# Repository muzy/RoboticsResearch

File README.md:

RoboticsResearch
================

Build a sustainable open-source robot platform affordable for everyone. This project is part of a student research project at the DHBW Mannheim, Germany.

ToDo
----

- [x] Create Repository 
- [X] Finish Introduction
- [WIP] Evaluation of the "state of the art"
- [WIP] Case studies
- [ ] Prototype 
- [ ] Prototype testing with designated target group
- [ ] Documentation

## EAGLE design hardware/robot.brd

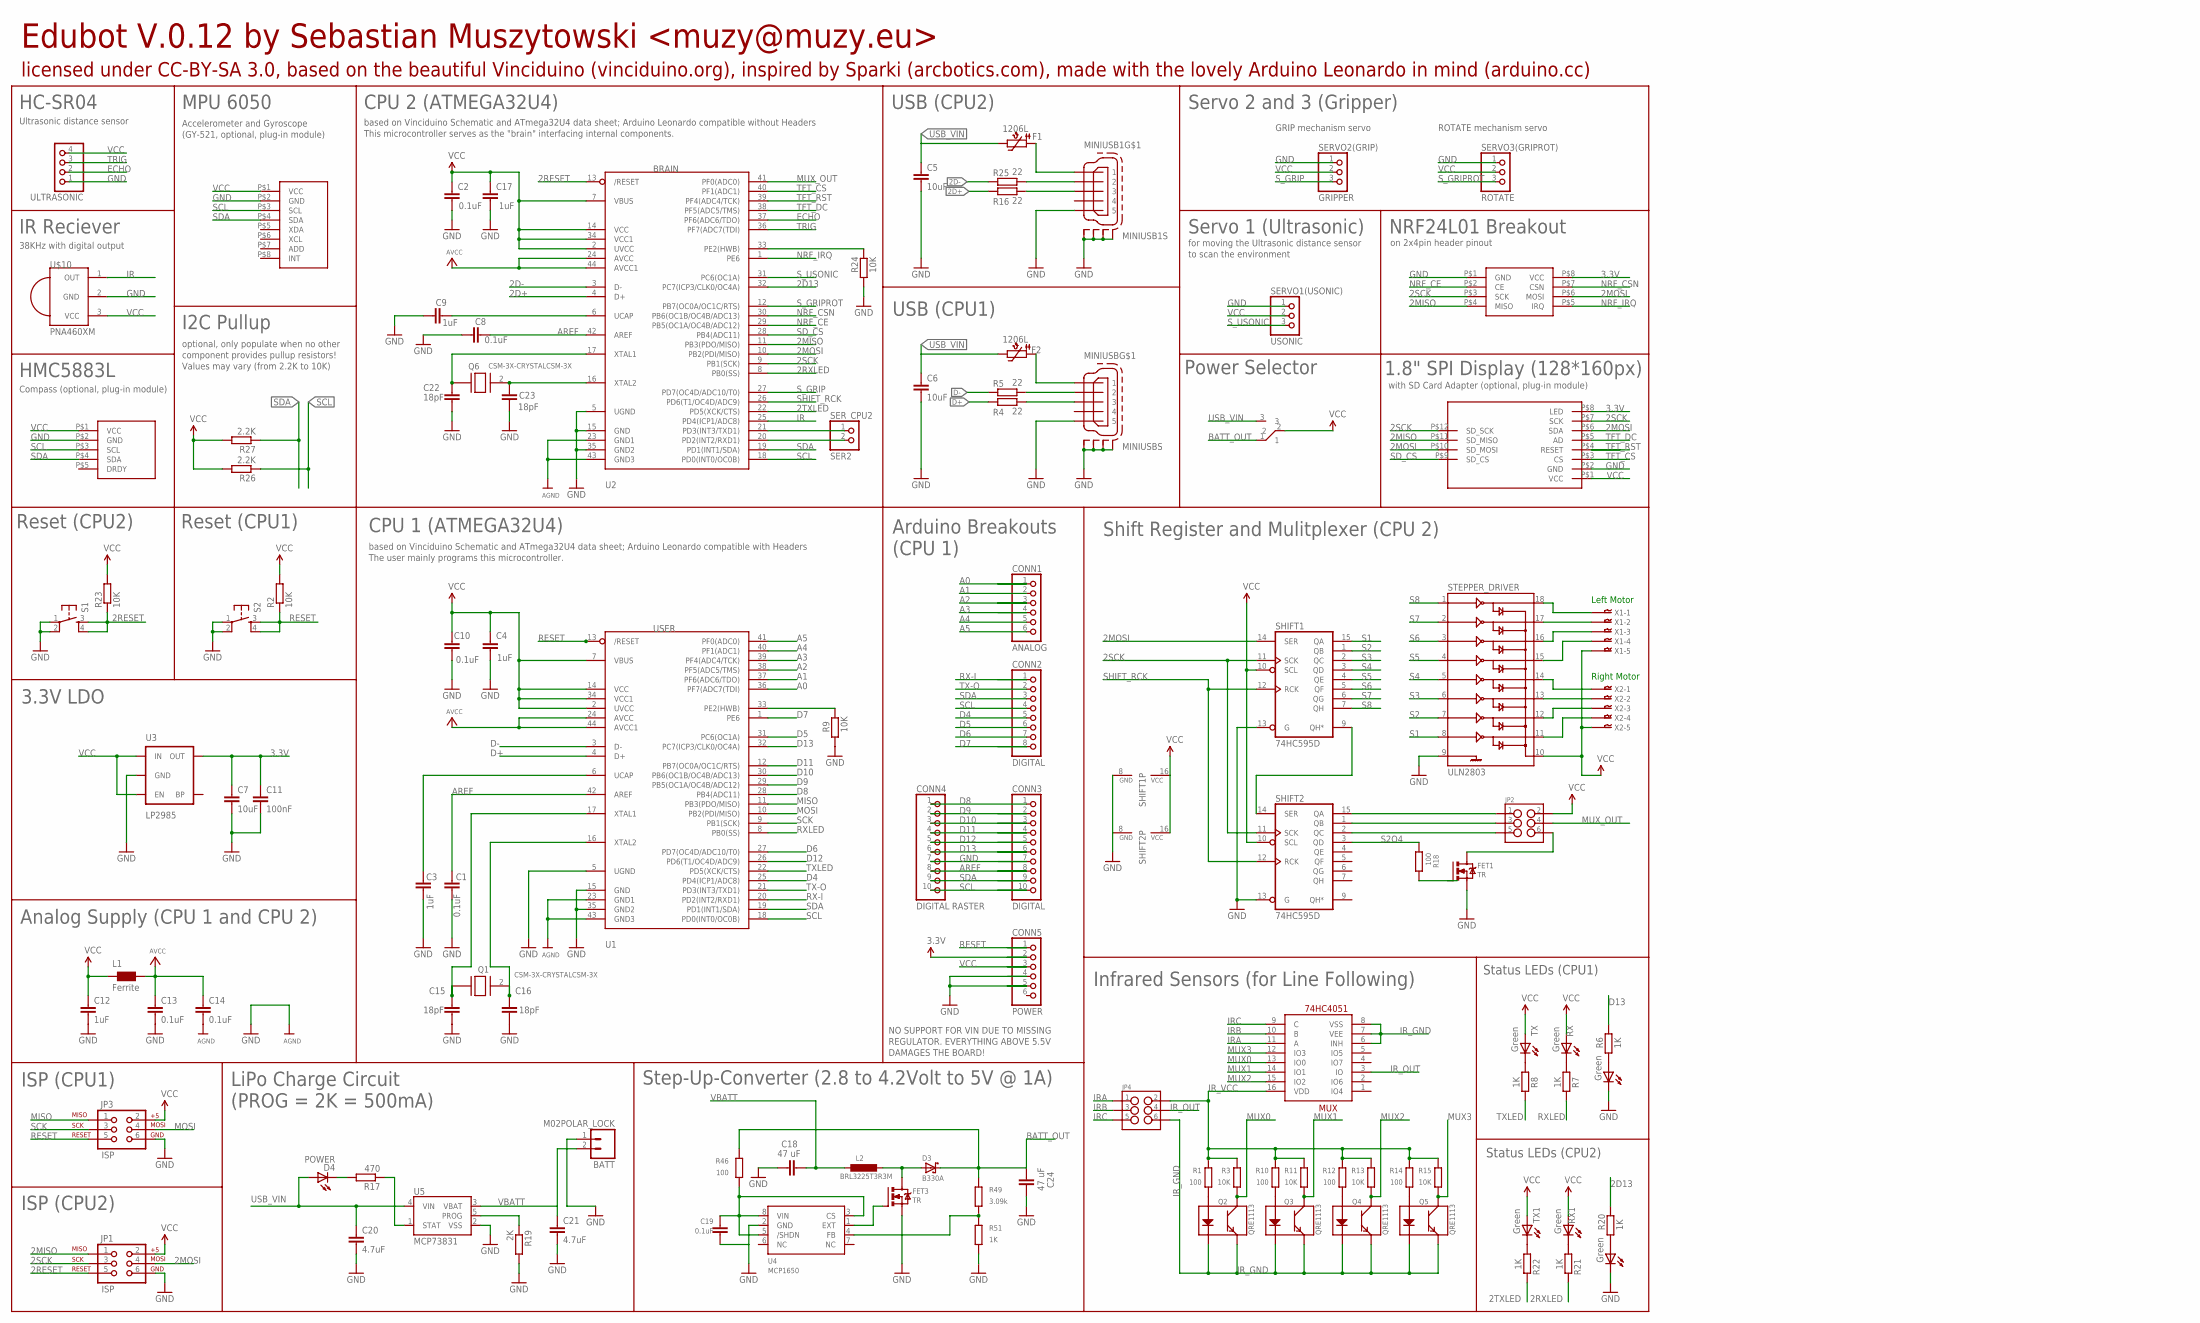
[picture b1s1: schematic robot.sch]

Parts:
BATT: M02POLAR_LOCK; MOLEX-1X2_LOCK
C1, C2, C8, C10, C13, C14, C19: 0.1uF; C1206
C3, C4, C9, C12, C17: 1uF; C1206
C5, C6, C7: 10uF; C1206
C11: 100nF; C1206
C15, C16, C22, C23: 18pF; C1206
C18, C24: 47 uF; C1206
C20, C21: 4.7uF; C1206
CONN1: ANALOG; 1X06-BIG
CONN2: DIGITAL; 1X08-BIG
CONN3: DIGITAL; 1X10-BIG
CONN4: DIGITAL RASTER; 1X10-BIG
CONN5: POWER; 1X06-BIG
D3: B330A; SMA
D4: POWER; LED-1206
D13, D13_2: Green; LED-1206
F1, F2: 1206L; 1206_PTC
FET1, FET3: TR; MICRO3
JP1, JP3: ISP; 2X3
JP2, JP4: M03X22X3_SILK_SM; 2X3
L1: Ferrite; 1206W
L2: BRL3225T3R3M; L3225P
MINIUSB, MINIUSB1: MINI-USB-SCHIELD-32005-201; 32005-201
MUX: 74HC4051; SO16
Q1, Q6: CSM-3X-CRYSTALCSM-3X; CSM-3X
Q2, Q3, Q4, Q5: QRE1113
R1, R10, R12, R14, R18, R46: 100; R1206
R2, R3, R9, R11, R13, R15, R23, R24: 10K; R1206
R4, R5, R16, R25: 22; R1206
R6, R7, R8, R20, R21, R22, R51: 1K; R1206
R17: 470; R1206
R19: 2K; R1206
R26, R27: 2.2K; R1206
R49: 3.09k; R1206
RX, RX1: Green; LED-1206
S1, S2: Reset; TACTILE_SWITCH_SMD
SERVO1(USONIC): USONIC; 1X03
SERVO2(GRIP): GRIPPER; 1X03
SERVO3(GRIPROT): ROTATE; 1X03
SER_CPU2: SER2; 1X02
SHIFT1, SHIFT2: 74HC595D; SO16
STEPPER_DRIVER: ULN2803; SO18L
SW1: SPDT; SPDT-PTH
TX, TX1: Green; LED-1206
U1: USER; TQFP44
U2: BRAIN; TQFP44
U3: LP2985; SOT23-5@1
U4: MCP1650; MSOP8
U5: MCP73831; SOT23-5
U$2: 1.8TFT+SD; 1.8TFTSD
U$3: GY-521
U$4: HMC5883L
U$5: NRF24L01+
U$10: PNA460XM
ULTRASONIC: PINHD-1X4; 1X04
X1, X2: 05-JST-B5B-XH-A; B5B-XH

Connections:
2D13: R20.1, U2.32 (PC7(ICP3/CLK0/OC4A))
2D+: R16.1, U2.4 (D+)
2D-: R25.1, U2.3 (D-)
2MISO: JP1.1, U2.11 (PB3(PDO/MISO)), U$2.P$11 (SD_MISO), U$5.P$4 (MISO)
2MOSI: JP1.4, SHIFT1.14 (SER), U2.10 (PB2(PDI/MISO)), U$2.P$6 (SDA), U$2.P$10 (SD_MOSI), U$5.P$6 (MOSI)
2RESET: JP1.5, R23.1, S1.3, S1.4, U2.13 (/RESET)
2RXLED: R21.1, U2.8 (PB0(SS))
2SCK: JP1.3, SHIFT1.11 (SCK), SHIFT2.11 (SCK), U2.9 (PB1(SCK)), U$2.P$7 (SCK), U$2.P$12 (SD_SCK), U$5.P$3 (SCK)
2TXLED: R22.1, U2.22 (PD5(XCK/CTS))
2XTAL1: C22.1, Q6.1, U2.17 (XTAL1)
2XTAL2: C23.1, Q6.2, U2.16 (XTAL2)
3.3V: C7.1, C11.1, CONN5.2, U3.5 (OUT), U$2.P$8 (LED), U$5.P$8 (VCC)
A0: CONN1.1, U1.36 (PF7(ADC7(TDI))
A1: CONN1.2, U1.37 (PF6(ADC6/TDO))
A2: CONN1.3, U1.38 (PF5(ADC5/TMS))
A3: CONN1.4, U1.39 (PF4(ADC4/TCK))
A4: CONN1.5, U1.40 (PF1(ADC1))
A5: CONN1.6, U1.41 (PF0(ADC0))
AREF: C1.2, C8.2, CONN3.8, CONN4.8, U1.42 (AREF), U2.42 (AREF)
AVCC: C13.1, C14.1, L1.2, U1.24 (AVCC), U1.44 (AVCC1), U2.24 (AVCC), U2.44 (AVCC1)
BATT_OUT: C24.1, D3.C, R46.2, R49.2, SW1.1
D4: CONN2.5, U1.25 (PD4(ICP1/ADC8))
D5: CONN2.6, U1.31 (PC6(OC1A))
D6: CONN2.7, U1.27 (PD7(OC4D/ADC10/T0))
D7: CONN2.8, U1.1 (PE6)
D8: CONN3.1, CONN4.1, U1.28 (PB4(ADC11))
D9: CONN3.2, CONN4.2, U1.29 (PB5(OC1A/OC4B/ADC12))
D10: CONN3.3, CONN4.3, U1.30 (PB6(OC1B/OC4B/ADC13))
D11: CONN3.4, CONN4.4, U1.12 (PB7(OC0A/OC1C/RTS))
D12: CONN3.5, CONN4.5, U1.26 (PD6(T1/OC4D/ADC9))
D13: CONN3.6, CONN4.6, R6.1, U1.32 (PC7(ICP3/CLK0/OC4A))
D+: R4.1, U1.4 (D+)
D-: R5.1, U1.3 (D-)
ECHO: U2.37 (PF6(ADC6/TDO)), ULTRASONIC.2
GND: BATT.1, C1.1, C2.2, C3.2, C4.2, C5.2, C6.2, C7.2, C8.1, C9.2, C10.2, C11.2, C12.2, C13.2, C14.2, C15.2, C16.2, C17.2, C18.1, C19.2, C20.2, C21.2, C22.2, C23.2, C24.2, CONN3.7, CONN4.7, CONN5.4, CONN5.5, D13.C, D13_2.C, FET1.2 (S), FET3.2 (S), JP1.6, JP3.6, MINIUSB.5, MINIUSB.M1 (S1), MINIUSB.M2 (S2), MINIUSB.M3 (S3), MINIUSB.M4 (S4), MINIUSB1.5, MINIUSB1.M1 (S1), MINIUSB1.M2 (S2), MINIUSB1.M3 (S3), MINIUSB1.M4 (S4), R9.2, R19.2, R24.2, R51.1, S1.1, S1.2, S2.1, S2.2, SERVO1(USONIC).1, SERVO2(GRIP).1, SERVO3(GRIPROT).1, SHIFT1.8 (GND), SHIFT1.13 (G), SHIFT2.8 (GND), SHIFT2.13 (G), STEPPER_DRIVER.9, U1.5 (UGND), U1.15 (GND), U1.23 (GND1), U1.35 (GND2), U1.43 (GND3), U2.5 (UGND), U2.15 (GND), U2.23 (GND1), U2.35 (GND2), U2.43 (GND3), U3.2 (GND), U4.2 (GND), U5.2 (VSS), U$2.P$2 (GND), U$3.P$2 (GND), U$4.P$2 (GND), U$5.P$1 (GND), U$10.2 (GND), ULTRASONIC.1
IR: U2.25 (PD4(ICP1/ADC8)), U$10.1 (OUT)
IRA: JP4.1, MUX.11 (A)
IRB: JP4.3, MUX.10 (B)
IRC: JP4.5, MUX.9 (C)
IR_GND: JP4.6, MUX.6 (INH), MUX.7 (VEE), MUX.8 (VSS), Q2.2 (K), Q2.4 (E), Q3.2 (K), Q3.4 (E), Q4.2 (K), Q4.4 (E), Q5.2 (K), Q5.4 (E)
IR_OUT: JP4.4, MUX.3 (IO)
IR_VCC: JP4.2, MUX.16 (VDD), R1.2, R3.2, R10.2, R11.2, R12.2, R13.2, R14.2, R15.2
MISO: JP3.1, U1.11 (PB3(PDO/MISO))
MOSI: JP3.4, U1.10 (PB2(PDI/MISO))
MUX0: MUX.13 (IO0), Q2.3 (C), R3.1
MUX1: MUX.14 (IO1), Q3.3 (C), R11.1
MUX2: MUX.15 (IO2), Q4.3 (C), R13.1
MUX3: MUX.12 (IO3), Q5.3 (C), R15.1
MUX_OUT: JP2.4, U2.41 (PF0(ADC0))
unnamed: R8.2, TX.C
unnamed: MINIUSB.2, R5.2
unnamed: SER_CPU2.1, U2.21 (PD3(INT3/TXD1))
unnamed: SER_CPU2.2, U2.20 (PD2(INT2/RXD1))
unnamed: MINIUSB.3, R4.2
unnamed: R9.1, U1.33 (PE2(HWB))
unnamed: D13.A, R6.2
unnamed: C9.1, U2.6 (UCAP)
unnamed: R7.2, RX.C
unnamed: Q2.1 (A), R1.1
unnamed: Q3.1 (A), R10.1
unnamed: Q4.1 (A), R12.1
unnamed: F2.1, MINIUSB.1
unnamed: Q5.1 (A), R14.1
unnamed: C3.1, U1.6 (UCAP)
unnamed: FET1.1 (G), R18.2
unnamed: R24.1, U2.33 (PE2(HWB))
unnamed: F1.1, MINIUSB1.1
unnamed: FET3.1 (G), U4.1 (EXT)
unnamed: R19.1, U5.5 (PROG)
unnamed: R17.1, U5.1 (STAT)
unnamed: D4.C, R17.2
unnamed: R49.1, R51.2, U4.4 (FB)
unnamed: D3.A, FET3.3 (D), L2.2
unnamed: C19.1, R46.1, U4.3 (CS), U4.5 (/SHDN), U4.8 (VIN)
unnamed: STEPPER_DRIVER.11, X2.P$4
unnamed: STEPPER_DRIVER.12, X2.P$3
unnamed: STEPPER_DRIVER.13, X2.P$2
unnamed: STEPPER_DRIVER.14, X2.P$1
unnamed: STEPPER_DRIVER.15, X1.P$4
unnamed: STEPPER_DRIVER.16, X1.P$3
unnamed: STEPPER_DRIVER.17, X1.P$2
unnamed: STEPPER_DRIVER.18, X1.P$1
unnamed: D13_2.A, R20.2
unnamed: R22.2, TX1.C
unnamed: R21.2, RX1.C
unnamed: MINIUSB1.2, R25.2
unnamed: MINIUSB1.3, R16.2
unnamed: JP2.1, SHIFT2.15 (QA)
unnamed: JP2.3, SHIFT2.1 (QB)
unnamed: JP2.5, SHIFT2.2 (QC)
unnamed: FET1.3 (D), JP2.6
NRF_CE: U2.29 (PB5(OC1A/OC4B/ADC12)), U$5.P$2 (CE)
NRF_CSN: U2.30 (PB6(OC1B/OC4B/ADC13)), U$5.P$7 (CSN)
NRF_IRQ: U2.1 (PE6), U$5.P$5 (IRQ)
RESET: CONN5.1, JP3.5, R2.1, S2.3, S2.4, U1.13 (/RESET)
RX-I: CONN2.1, U1.20 (PD2(INT2/RXD1))
RXLED: R7.1, U1.8 (PB0(SS))
S1: SHIFT1.15 (QA), STEPPER_DRIVER.8
S1OVERFLOW: SHIFT1.9 (QH*), SHIFT2.14 (SER)
S2: SHIFT1.1 (QB), STEPPER_DRIVER.7
S2O4: R18.1, SHIFT2.3 (QD)
S3: SHIFT1.2 (QC), STEPPER_DRIVER.6
S4: SHIFT1.3 (QD), STEPPER_DRIVER.5
S5: SHIFT1.4 (QE), STEPPER_DRIVER.4
S6: SHIFT1.5 (QF), STEPPER_DRIVER.3
S7: SHIFT1.6 (QG), STEPPER_DRIVER.2
S8: SHIFT1.7 (QH), STEPPER_DRIVER.1
SCK: JP3.3, U1.9 (PB1(SCK))
SCL: CONN2.4, CONN3.10, CONN4.10, R26.1, U1.18 (PD0(INT0/OC0B)), U2.18 (PD0(INT0/OC0B)), U$3.P$3 (SCL), U$4.P$3 (SCL)
SDA: CONN2.3, CONN3.9, CONN4.9, R27.1, U1.19 (PD1(INT1/SDA)), U2.19 (PD1(INT1/SDA)), U$3.P$4 (SDA), U$4.P$4 (SDA)
SD_CS: U2.28 (PB4(ADC11)), U$2.P$9 (SD_CS)
SHIFT_RCK: SHIFT1.12 (RCK), SHIFT2.12 (RCK), U2.26 (PD6(T1/OC4D/ADC9))
S_GRIP: SERVO2(GRIP).3, U2.27 (PD7(OC4D/ADC10/T0))
S_GRIPROT: SERVO3(GRIPROT).3, U2.12 (PB7(OC0A/OC1C/RTS))
S_USONIC: SERVO1(USONIC).3, U2.31 (PC6(OC1A))
TFT_CS: U2.40 (PF1(ADC1)), U$2.P$3 (CS)
TFT_DC: U2.38 (PF5(ADC5/TMS)), U$2.P$5 (AD)
TFT_RST: U2.39 (PF4(ADC4/TCK)), U$2.P$4 (RESET)
TRIG: U2.36 (PF7(ADC7(TDI)), ULTRASONIC.3
TX-O: CONN2.2, U1.21 (PD3(INT3/TXD1))
TXLED: R8.1, U1.22 (PD5(XCK/CTS))
USB_VIN: C5.1, C6.1, C20.1, D4.A, F1.2, F2.2, SW1.3, U5.4 (VIN)
VBATT: BATT.2, C18.2, C21.1, L2.1, U5.3 (VBAT)
VCC: C2.1, C4.1, C10.1, C12.1, C17.1, CONN5.3, JP1.2, JP2.2, JP3.2, L1.1, R2.2, R23.2, R26.2, R27.2, RX.A, RX1.A, SERVO1(USONIC).2, SERVO2(GRIP).2, SERVO3(GRIPROT).2, SHIFT1.10 (SCL), SHIFT1.16 (VCC), SHIFT2.10 (SCL), SHIFT2.16 (VCC), STEPPER_DRIVER.10, SW1.2, TX.A, TX1.A, U1.2 (UVCC), U1.7 (VBUS), U1.14 (VCC), U1.34 (VCC1), U2.2 (UVCC), U2.7 (VBUS), U2.14 (VCC), U2.34 (VCC1), U3.1 (IN), U3.3 (EN), U$2.P$1 (VCC), U$3.P$1 (VCC), U$4.P$1 (VCC), U$10.3 (VCC), ULTRASONIC.4, X1.P$5, X2.P$5
XTAL1: C15.1, Q1.1, U1.17 (XTAL1)
XTAL2: C16.1, Q1.2, U1.16 (XTAL2)

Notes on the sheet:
USB (CPU1)
Reset (CPU1)
ISP (CPU1)
Analog Supply (CPU 1 and CPU 2)
Arduino Breakouts (CPU 1)
CPU 1 (ATMEGA32U4)
Left Motor
Right Motor
Shift Register and Mulitplexer (CPU 2)
Infrared Sensors (for Line Following)
Step-Up-Converter (2.8 to 4.2Volt to 5V @ 1A)
LiPo Charge Circuit (PROG = 2K = 500mA)
Status LEDs (CPU1)
Status LEDs (CPU2)
ISP (CPU2)
3.3V LDO
based on Vinciduino Schematic and ATmega32U4 data sheet; Arduino Leonardo compatible with Headers The user mainly programs this microcontroller.
Reset (CPU2)
CPU 2 (ATMEGA32U4)
based on Vinciduino Schematic and ATmega32U4 data sheet; Arduino Leonardo compatible without Headers This microcontroller serves as the "brain" interfacing internal components.
USB (CPU2)
Power Selector
1.8" SPI Display (128*160px)
with SD Card Adapter (optional, plug-in module)
I2C Pullup
optional, only populate when no other component provides pullup resistors! Values may vary (from 2.2K to 10K)
HMC5883L
Compass (optional, plug-in module)
MPU 6050
Accelerometer and Gyroscope (GY-521, optional, plug-in module)
NRF24L01 Breakout
on 2x4pin header pinout
IR Reciever
38KHz with digital output
HC-SR04
Ultrasonic distance sensor
Servo 1 (Ultrasonic)
for moving the Ultrasonic distance sensor to scan the environment
Servo 2 and 3 (Gripper)
GRIP mechanism servo

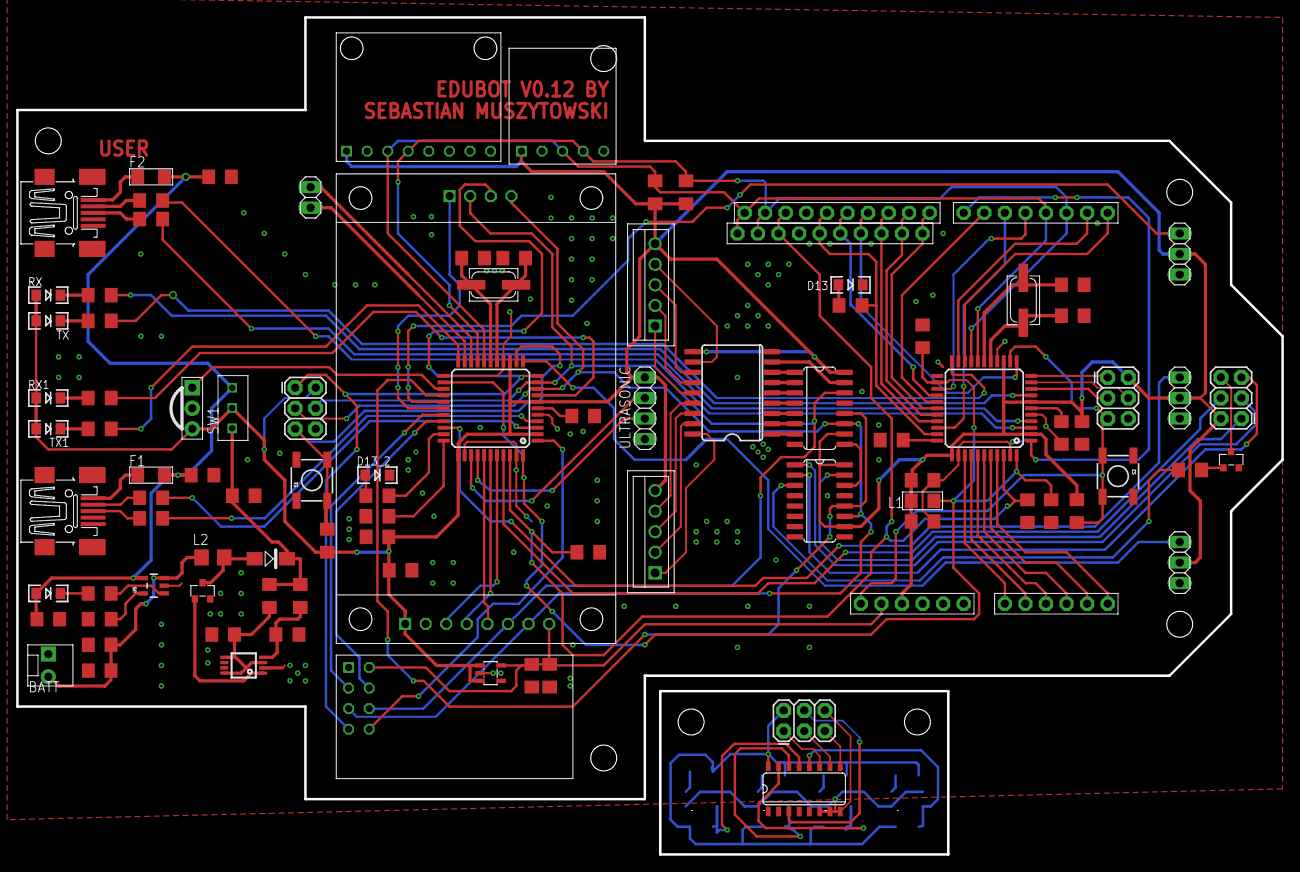
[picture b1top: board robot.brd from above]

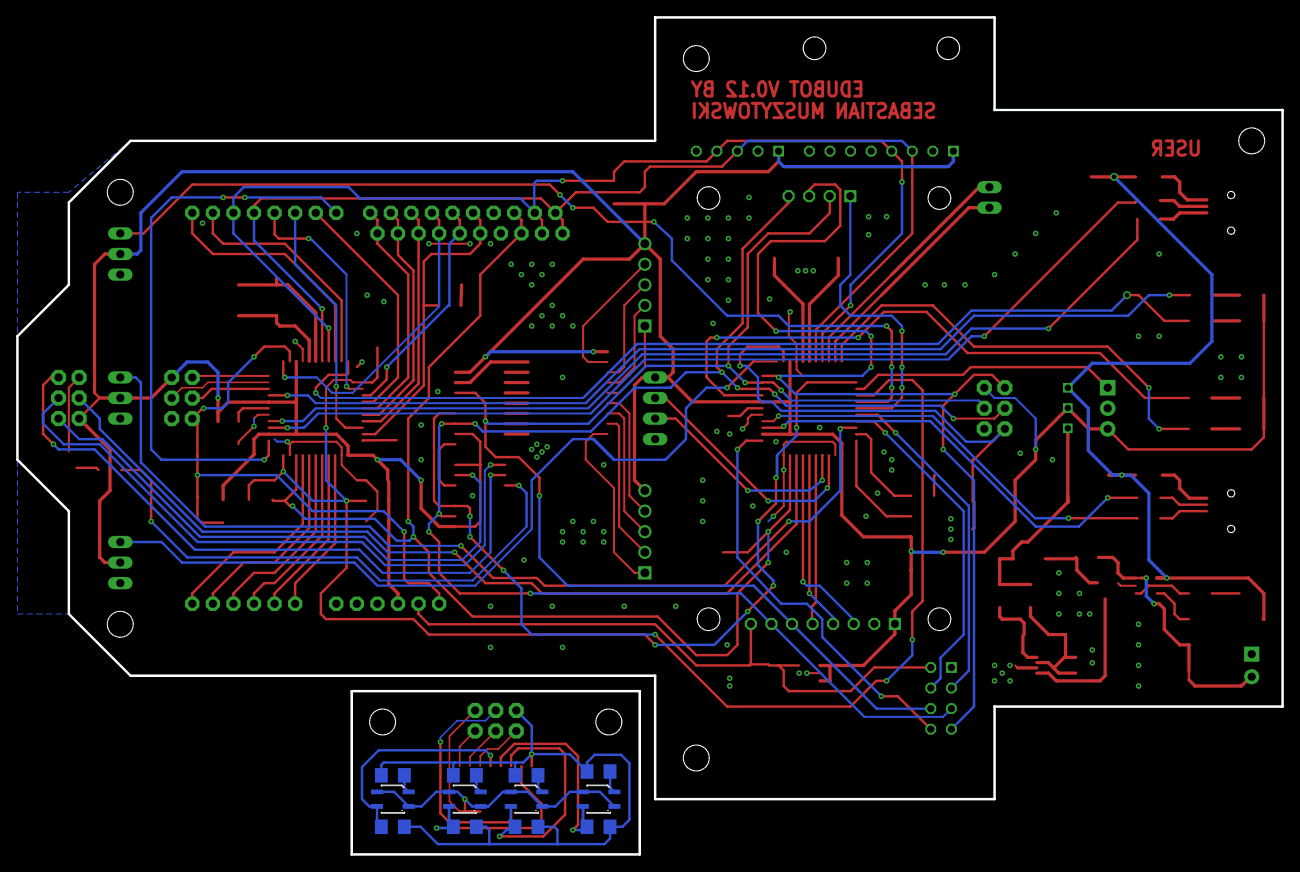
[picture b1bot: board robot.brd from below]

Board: 2 copper layers, 156.2 x 103.3 mm, 110 parts (12 on the bottom side), 126 nets.

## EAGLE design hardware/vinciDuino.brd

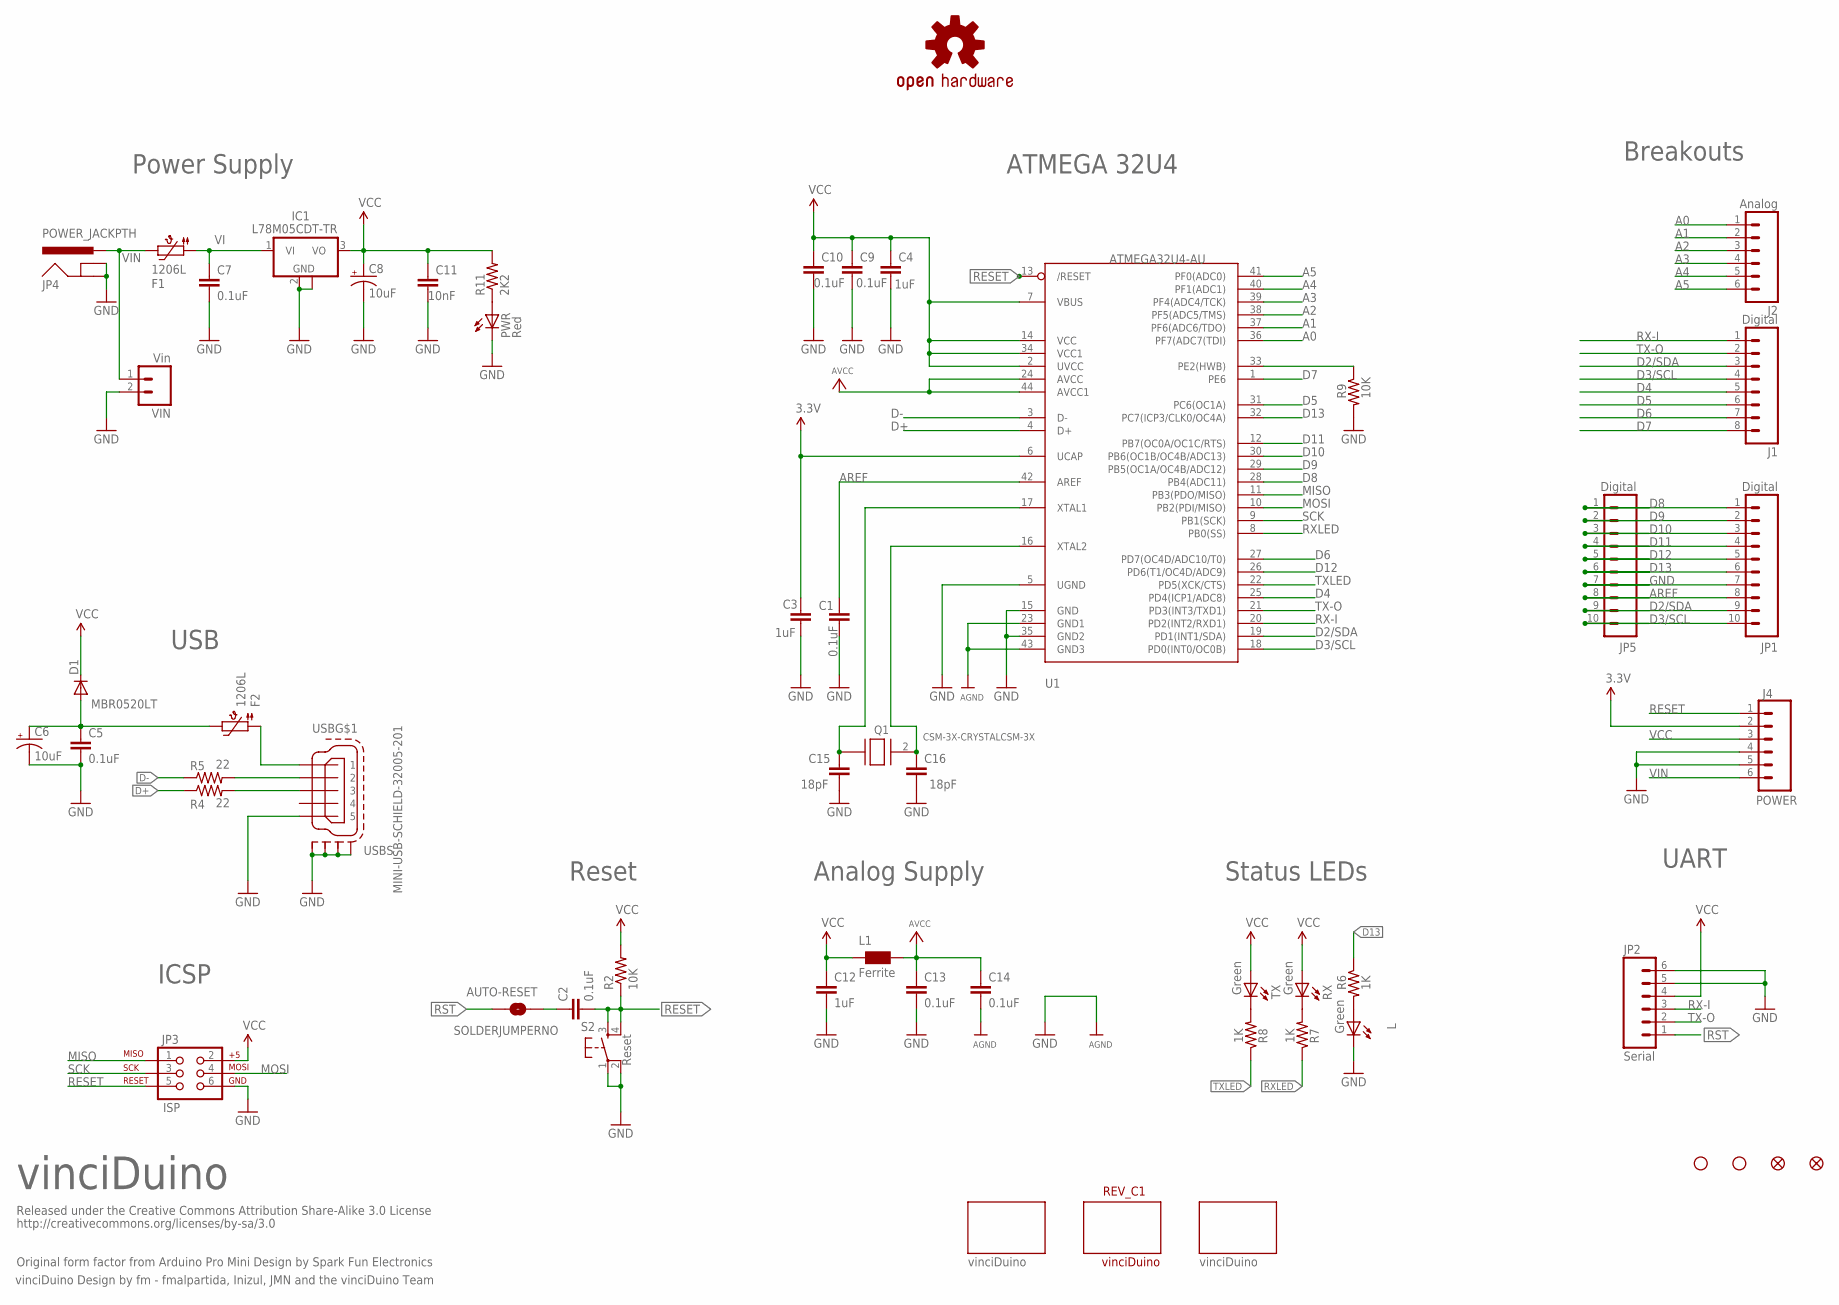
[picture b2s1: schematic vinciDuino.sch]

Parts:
AUTO-RESET: SOLDERJUMPERNO; SJ_2S-NO
C1, C2, C5, C7, C9, C10, C13, C14: 0.1uF; 1206
C3, C4, C12: 1uF; 1206
C6, C8: 10uF; EIA3216
C11: 10nF; 1206
C15, C16: 18pF; 1206
D1: MBR0520LT; SOD123
F1, F2: 1206L; 1206_PTC
IC1: L78M05CDT-TR; SOT-223-DPAK
J1: Digital; 1X08
J2: Analog; 1X06
J4: POWER; 1X06
JP1, JP5: Digital; 1X10
JP2: Serial; 1X06
JP3: ISP; 2X3
JP4: POWER_JACKPTH; POWER_JACK_PTH
L: Green; LED-1206
L1: Ferrite; 1206W
PWR: Red; LED-1206
Q1: CSM-3X-CRYSTALCSM-3X; CSM-3X
R2, R9: 10K; R1206
R4, R5: 22; R1206
R6, R7, R8: 1K; R1206
R11: 2K2; R1206
REV_C1: vinciDuino; ARDUINO_FORUM
RX: Green; LED-1206
S2: Reset; TACTILE_SWITCH_SMD
TX: Green; LED-1206
U1: ATMEGA32U4-AU; TQFP44
U$1: VINCIDUINO_; VINCIDUINO
U$2, U$4: FIDUCIAL1X2; FIDUCIAL-1X2
U$3: VINCIDUINO_15; VINCIDUINO_VSMAL
U$9, U$10: STAND-OFF
U$14: OSHW-LOGOS; OSHW-LOGO-S
USB: MINI-USB-SCHIELD-32005-201; 32005-201
VIN: Vin; 1X02_NO_SILK

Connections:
3.3V: C3.1, J4.2, U1.6 (UCAP)
A0: J2.1, U1.36 (PF7(ADC7(TDI))
A1: J2.2, U1.37 (PF6(ADC6/TDO))
A2: J2.3, U1.38 (PF5(ADC5/TMS))
A3: J2.4, U1.39 (PF4(ADC4/TCK))
A4: J2.5, U1.40 (PF1(ADC1))
A5: J2.6, U1.41 (PF0(ADC0))
AREF: C1.2, JP1.8, JP5.8, U1.42 (AREF)
AVCC: C13.1, C14.1, L1.2, U1.24 (AVCC), U1.44 (AVCC1)
D2/SDA: J1.3, JP1.9, JP5.9, U1.19 (PD1(INT1/SDA))
D3/SCL: J1.4, JP1.10, JP5.10, U1.18 (PD0(INT0/OC0B))
D4: J1.5, U1.25 (PD4(ICP1/ADC8))
D5: J1.6, U1.31 (PC6(OC1A))
D6: J1.7, U1.27 (PD7(OC4D/ADC10/T0))
D7: J1.8, U1.1 (PE6)
D8: JP1.1, JP5.1, U1.28 (PB4(ADC11))
D9: JP1.2, JP5.2, U1.29 (PB5(OC1A/OC4B/ADC12))
D10: JP1.3, JP5.3, U1.30 (PB6(OC1B/OC4B/ADC13))
D11: JP1.4, JP5.4, U1.12 (PB7(OC0A/OC1C/RTS))
D12: JP1.5, JP5.5, U1.26 (PD6(T1/OC4D/ADC9))
D13: JP1.6, JP5.6, R6.1, U1.32 (PC7(ICP3/CLK0/OC4A))
D+: R4.1, U1.4 (D+)
D-: R5.1, U1.3 (D-)
GND: C1.1, C3.2, C4.2, C5.2, C6.C (-), C7.2, C8.C (-), C9.2, C10.2, C11.2, C12.2, C13.2, C14.2, C15.2, C16.2, IC1.2 (GND), IC1.4 (GND), J4.4, J4.5, JP1.7, JP2.5, JP2.6, JP3.6, JP4.GND, JP4.GNDBREAK, JP5.7, L.C, PWR.C, R9.2, S2.1, S2.2, U1.5 (UGND), U1.15 (GND), U1.23 (GND1), U1.35 (GND2), U1.43 (GND3), USB.5, USB.M1 (S1), USB.M2 (S2), USB.M3 (S3), USB.M4 (S4), VIN.2
MISO: JP3.1, U1.11 (PB3(PDO/MISO))
MOSI: JP3.4, U1.10 (PB2(PDI/MISO))
unnamed: R8.2, TX.C
unnamed: R5.2, USB.2
unnamed: C16.1, Q1.2, U1.16 (XTAL2)
unnamed: C15.1, Q1.1, U1.17 (XTAL1)
unnamed: R4.2, USB.3
unnamed: R9.1, U1.33 (PE2(HWB))
unnamed: L.A, R6.2
unnamed: AUTO-RESET.2, C2.1
unnamed: R7.2, RX.C
unnamed: F2.1, USB.1
unnamed: PWR.A, R11.1
RESET: C2.2, J4.1, JP3.5, R2.1, S2.3, S2.4, U1.13 (/RESET)
RST: AUTO-RESET.1, JP2.1
RX-I: J1.1, JP2.3, U1.20 (PD2(INT2/RXD1))
RXLED: R7.1, U1.8 (PB0(SS))
SCK: JP3.3, U1.9 (PB1(SCK))
TX-O: J1.2, JP2.2, U1.21 (PD3(INT3/TXD1))
TXLED: R8.1, U1.22 (PD5(XCK/CTS))
VBUS: C5.1, C6.A (+), D1.A, F2.2
VCC: C4.1, C8.A (+), C9.1, C10.1, C11.1, C12.1, D1.C, IC1.3 (VO), J4.3, JP2.4, JP3.2, L1.1, R2.2, R11.2, RX.A, TX.A, U1.2 (UVCC), U1.7 (VBUS), U1.14 (VCC), U1.34 (VCC1)
VI: C7.1, F1.1, IC1.1 (VI)
VIN: F1.2, J4.6, JP4.PWR, VIN.1

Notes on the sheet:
Released under the Creative Commons Attribution Share-Alike 3.0 License
http://creativecommons.org/licenses/by-sa/3.0
Original form factor from Arduino Pro Mini Design by Spark Fun Electronics
vinciDuino Design by fm - fmalpartida, Inizul, JMN and the vinciDuino Team
Power Supply
USB
Reset
ICSP
Analog Supply
Status LEDs
UART
Breakouts
ATMEGA 32U4
vinciDuino

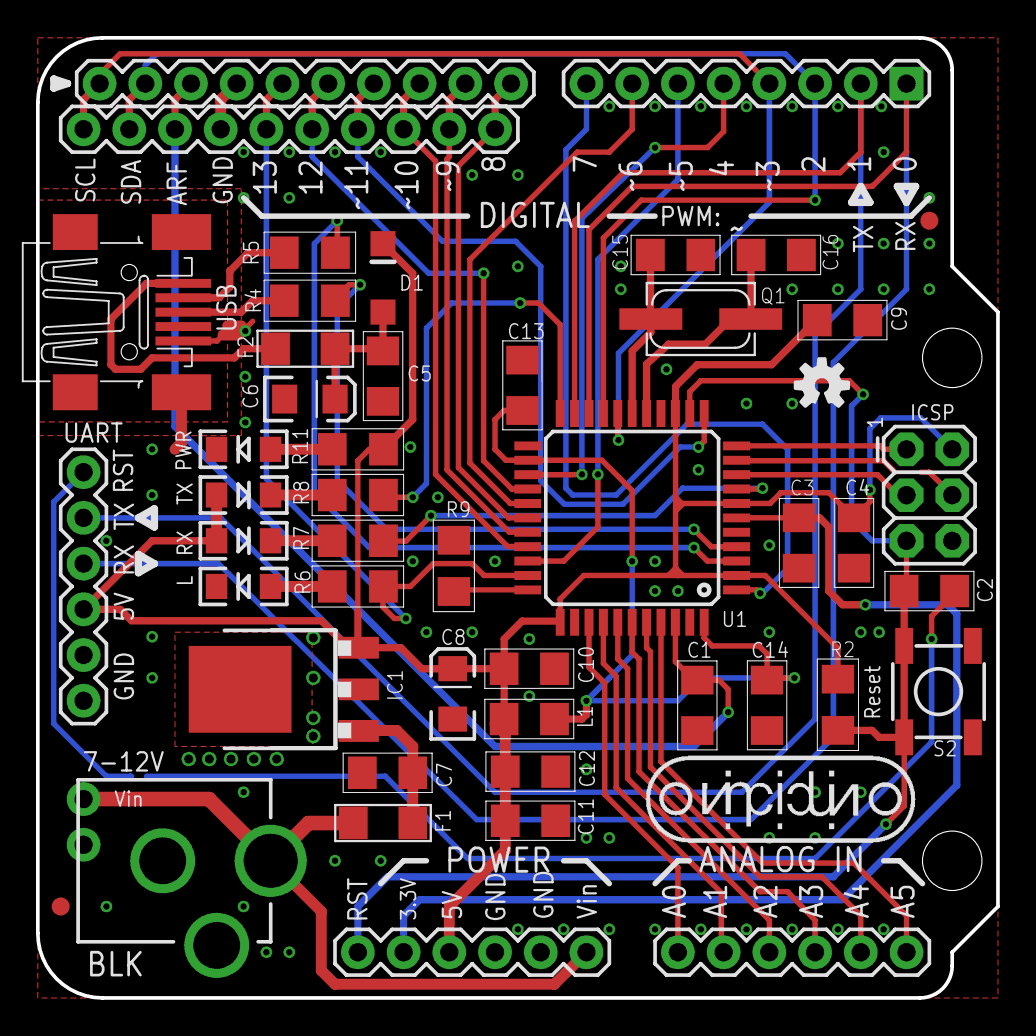
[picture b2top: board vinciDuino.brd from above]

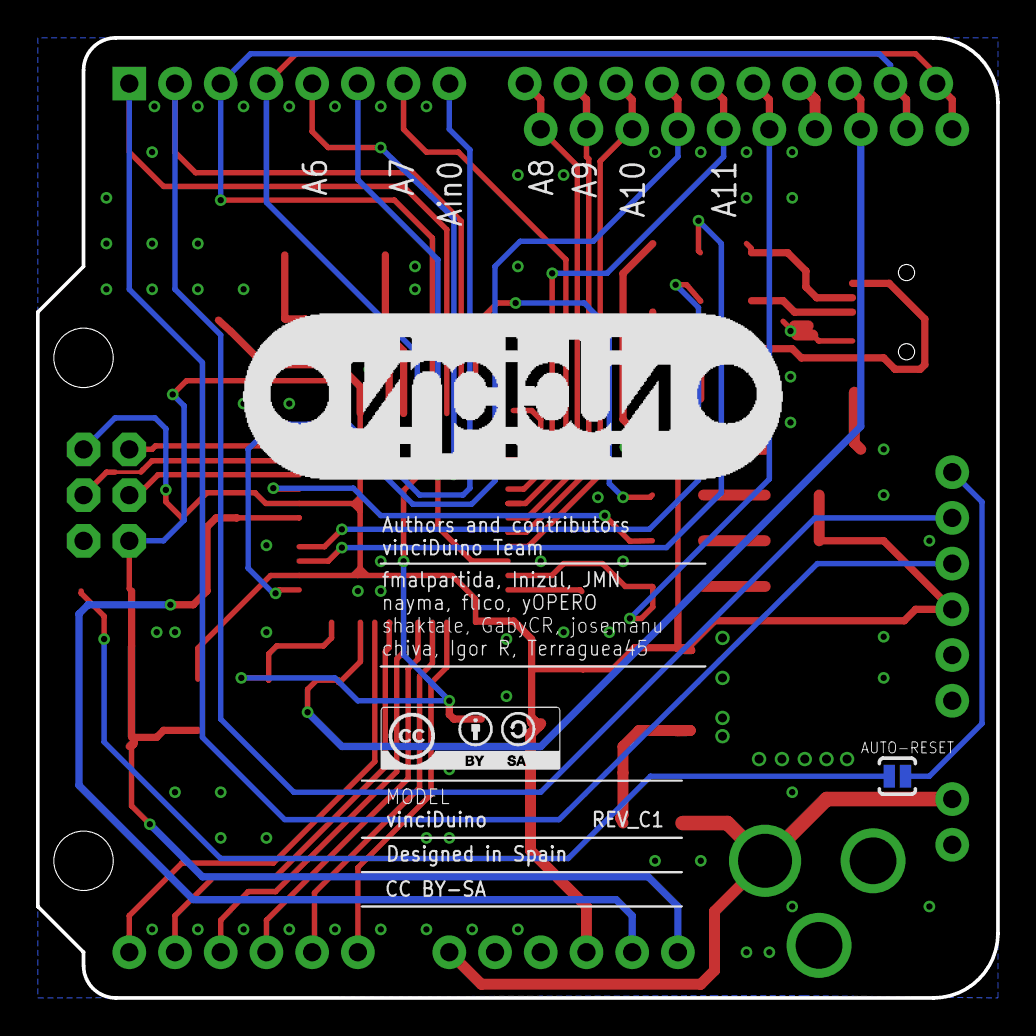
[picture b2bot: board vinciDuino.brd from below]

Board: 2 copper layers, 53.3 x 53.3 mm, 56 parts (4 on the bottom side), 48 nets.

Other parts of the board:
U$13: SA-BY

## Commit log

2013-09-10 add explanations
2013-10-06 just a draft
2013-10-07 autocommited by makefile
2013-10-28 Rename schematic to hardware. Add Evaluation sheet
2013-11-02 Fix Typo, add PWM and GPIO
2014-03-10 zeugs
2014-03-13 new revision
2014-03-15 new revision (fuck yeah)
2014-03-15 final?
2014-03-15 i can haz gerber
2014-04-11 add chapter about MUX/demux
2014-05-03 stuff
2014-05-04 more stuff
2014-05-08 changed things to paper
2014-05-12 paper

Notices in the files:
hardware/robot.sch:
licensed under CC-BY-SA 3.0, based on the beautiful Vinciduino (vinciduino.org), inspired by Sparki (arcbotics.com), made with the lovely Arduino Leonardo in mind (arduino.cc)
parts and their libraries:
SparkFun-Connectors: Licensing: Creative Commons ShareAlike 4.0 International - https://creativecommons.org/licenses/by-sa/4.0
fmc: CC BY-SA
